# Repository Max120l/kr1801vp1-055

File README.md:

# A replacement for the КР1801ВП1-055

The 055 is a Soviet gate-array bus transceiver: sixteen bidirectional lines plus
three unidirectional buffers, in a 42-pin through-hole package with the pins in
four staggered rows. It cannot be bought, and the only machine known to use it
is the **Elektronika MS 0511 (UKNC)**,
where it is **D22** — sitting between the peripheral processor and the MPI bus,
so when it fails the machine fails in ways that look like everything except a
transceiver.

This repository works out what the chip does, proves a substitute built from
catalogue parts behaves identically, and lists what to buy.

*The part and its replacement, at the same scale. Left: the original, date code
8905, with its pins in the four staggered rows that took three board revisions
to get right. Right: rev C, carrying two 74AHCT245 and a 74AHCT125 in
essentially the original's footprint.*

**Status: built, fitted, and proven — cold and hot.**

A substitute on adapter revision C runs as D22 in the machine this project came
from. It passes the machine's own ТЕСТИРОВАНИЕ fourteen times with ОШИБОК 0, and
a purpose-built bus soak moved **107 MiB through the chip in 1719 passes with
zero errors** — fourteen million of them transitions in which all sixteen lines
reverse at once, which is the one case this design cannot reproduce the
original's answer to. The last 90 passes were run with the board deliberately
heated until it was too hot to touch.

That matters because the fault was thermal and nothing else: the original ran
about ten minutes from cold, died, and recovered within seconds of being cooled.
It was localised two independent ways in September 2026 — cooling D22 alone kept
the machine up, and a CPU-side RAM canary (onerom-1801re2, `diag/canary`) stayed
clean for hundreds of passes while the peripheral processor behind D22 died hot.

Details, figures and what is still unmeasured:
[TESTING.md](docs/TESTING.md#4-the-result).

*Adapter revision C in the socketed D22 site of the MS 0511. The three chips are
the two 74AHCT245 and the 74AHCT125; the board stands about 10 mm above the
motherboard, so check what sits above the site before closing the case.*

## The two findings

**It has no state.** Every cell in the die schematic is a gate, a buffer or an
inverter — no flip-flop, no latch, no clock, no feedback path. That was the
question gating this project, because a stateful control block would have forced
a programmable part. It does not: three ordinary chips reproduce it exactly.

**It does not invert.** Each path carries an even number of inversions — four in
the low byte, two in the high byte, zero in the three-bit buffer. The `nA0–nA15`
pin naming records the bus's active-low convention, not an inversion across this
part. So the substitute is the **74x245**, not the '640.

That second one is a correction, and it is now settled on hardware rather than
only on the die. Earlier notes in the sibling
[onerom-1801re2](https://github.com/Max120l/onerom-1801re2) repository called
the part inverting and recommended the '640, reasoning from the bus rather than
from the die. Building that would have inverted the machine's entire address and
data bus. `make mutants` builds it deliberately and shows the test rejecting it —
and a '245-based board now runs in the machine, which a non-inverting substitute
for an inverting part could not do.

## The substitute

| ref | part | |
|---|---|---|
| U1, U2 | 74AHCT245 | the sixteen bidirectional lines, one per byte |
| U3 | 74AHCT125 | C0–C2 → A0–A2, permanently enabled |
| C1–C4 | 100 nF × 3, 10 µF | decoupling |

`nA` to the '245 A side, `V`/`W` to the B side, pin 20 straight to `DIR`, pin 41
straight to `/OE`. No glue logic at all. Full pin mapping, part-choice reasoning
and the timing comparison are in [DESIGN.md](docs/DESIGN.md).

## Proving it

```console
$ make check                 # substitute vs the original's own gate-array cells
60 checks, 0 mismatches
EQUIVALENT

$ make mutants               # and the test can actually fail
  caught      MUTANT_INVERTING
  caught      MUTANT_DIR
  caught      MUTANT_C_GATED
all mutants caught
```

The reference model is structural: it instantiates the k1801 project's own cell
library, wired the way the die schematic wires it, rather than describing what
the chip is believed to do. Needs Icarus Verilog.

The machine then agreed with the simulation: a board built to this design runs
as D22, and all three mutants above describe mistakes that would have stopped it
running at all — see [TESTING.md](docs/TESTING.md#4-the-result).

## Files

| | |
|---|---|
| [docs/LOGIC.md](docs/LOGIC.md) | what the chip does, traced cell by cell, with the delays |
| [docs/DESIGN.md](docs/DESIGN.md) | the substitute: parts, pin mapping, timing, what is lost |
| [docs/TESTING.md](docs/TESTING.md) | bench check, the proof, and bringing it up in the machine |
| [adapter/](adapter/README.md) | the 42-pin adapter board: generator, routing, gerbers |
| [bustest/](bustest/README.md) | a FODOS volume of adversarial bus patterns, for the worst case ТЕСТИРОВАНИЕ never produces |
| `rtl/vp1_055_orig.v` | the original, from its own cells |
| `rtl/vp1_055_repl.v` | the substitute, from gate primitives |
| `rtl/lib_1801.v` | the k1801 cell library, vendored unmodified |
| `sim/tb_equiv.v` | the equivalence testbench |

## What is not done

- **The PCB is at revision C** — [adapter/](adapter/README.md): a 31 × 32 mm
  two-layer board with the three chips on top and a 42-pin field in the
  measured four-row site geometry underneath, generated and routed by script,
  gerbers included. Revision A was fabricated and did not fit: it mirrored the
  two sides, and the real package's sides are translated copies (rows
  10 · 11 · 10 · 11 with pin 1 top-left, pin 1 in the inner row). Rev C
  corrects the field, and is the revision now fabricated and running in the
  machine.
- **No scope has ever been on the nOE release edge**, of either part. It is the
  one claim in [DESIGN.md](docs/DESIGN.md#timing) still resting on reasoning
  rather than measurement — though a repair that survives a hot worst-case soak
  is strong circumstantial evidence the margin is there. See
  [TESTING.md](docs/TESTING.md#1-the-polarity-check).
- **The delay stagger is still not reproduced**, and now demonstrably does not
  need to be — at least not cold. The original spread its two bytes 7.5 ns apart
  to limit the supply transient when sixteen drivers switch; two identical '245s
  switch together, and the answer here is decoupling. Thirteen million
  deliberate worst-case transitions have now gone through without a bad bit, so
  this is a solved problem rather than an out-voted one. Hot is still untested.

## Credits

The die schematic, the pin description and the cell library are the work of the
[1801BM1/k1801](https://github.com/1801BM1/k1801) project, which reverse
engineered this and a dozen sibling chips from die photographs. None of this
would be possible without it. See [THIRD-PARTY.md](THIRD-PARTY.md).

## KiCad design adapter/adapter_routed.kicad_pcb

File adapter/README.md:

# The adapter board

A 31 × 32 mm two-layer board that plugs into the socketed D22 site and carries
the substitute: two 74AHCT245 for the sixteen bidirectional lines, one
74AHCT125 for C0–C2 → A0–A2, decoupling, and underneath a field of 42 pins in
the original package's pattern. No glue logic — pin 20 goes straight to the
'245s' DIR (its sense already matches: high = nA drives V/W) and pin 41 to
their /OE. The logic is the one proven equivalent in `sim/`.

*Rev C fitted. The site is socketed with individual machined receptacles, as
described under Form factor in [DESIGN.md](../docs/DESIGN.md#form-factor), so
the original, a sourced replacement and this board all plug into the same
holes.*

`vp1-055-adapter-gerbers.zip` is the fab package (two layers, 0.2 mm tracks,
0.15 mm clearance, 0.7/0.3 mm vias, GND pours — any prototype fab).
`adapter_routed.kicad_pcb` is the routed board: 330 segments, 18 vias, every
connection routed, DRC clean.

## Routing practice

Checked against the usual two-layer rules (JLCPCB's routing best-practice
list, September 2026):

| rule | this board |
|---|---|
| signal width 8–10 mil | 0.2 mm (8 mil) everywhere |
| power wider | VCC/GND at 0.3 mm wherever the neighbours allow (about half their length); the rest 0.2 mm. Three AHCT chips draw a few tens of mA, so 8 mil is electrically fine either way |
| clearance ≥ 4 mil | 0.15 mm (6 mil) minimum, measured |
| 45° bends, no acute angles | 274 bends at 45°, 6 right angles, no acute ones |
| via ring ≥ 0.18–0.25 mm | 0.7 mm pad on a 0.3 mm drill: 0.2 mm ring |
| hole-to-hole ≥ 0.2 mm | 0.53 mm minimum |
| copper-to-edge ≥ 0.2 mm | pours stop 0.5 mm inside the edge, everything else more |
| reference plane / return path | solid GND pour on the bottom (≈600 mm², 60 % of the board) under the top-layer signal runs, a smaller one on top, stitched by the GND pins and vias |
| decoupling next to the VCC pin | each 100 nF within 3.6 mm of its chip's VCC pin; 10 µF bulk at the '125 |
| 3W spacing | not met in the bus bundles (0.35 mm centre-to-centre). Irrelevant at these edge rates and lengths; noted for honesty |
| silk ≥ 1 mm text, clear of pads | 1 mm text, pads knocked out of the silk in the export |
| DRC zero errors | yes, with the design's own rules loaded (see `polish_adapter.py` for why that matters) |

## The site, as measured

The КР1801ВП1 package is through-hole, 42 pins in **four staggered rows**:

| | |
|---|---|
| pitch within a row | 2.5 mm |
| consecutive pin numbers along a side | 1.25 mm (they alternate rows) |
| inner row to outer row, same side | 2.5 mm |
| outer row to outer row | 25.0 mm |
| pins | 0.5 mm square; standard machined receptacles fit |
| numbering | pin 1 at the dimple corner, **inner** row; down the left side, up the right (DIP order) |
| rows | with pin 1 top-left, **10 · 11 · 10 · 11** from left to right. The two sides are *translated* copies, not mirror images: the 11-pin row (the one that reaches the end positions) is the **inner** row on the pin-1 side and the **outer** row on the pin-22 side. Pins 1 and 21 are inboard, pins 22 and 42 outboard. |

**Revision C** is the current board (`REV C` on both silks). Revision A was
fabricated with the two sides mirrored (11 · 10 · 10 · 11): its right side
fits the site, its left side has the two rows swapped. Revision B guessed the
parity the other way round (11 · 10 · 11 · 10) and was never fabricated. Rev A
boards remain usable as the bench carrier in
[TESTING.md](../docs/TESTING.md) if the left-side pins are wired instead of
plugged.

Measured on the MS 0511 board in September 2026. If a different board or
package revision disagrees, the numbers live in one dictionary at the top of
`build_adapter.py`.

## Parts

Also as [`BOM.csv`](BOM.csv), with quantities, DigiKey and Mouser numbers
and the 42 socket receptacles for the machine side.

| ref | part | package |
|---|---|---|
| U1, U2 | 74AHCT245 (SN74AHCT245PWR) | TSSOP-20 |
| U3 | 74AHCT125 (SN74AHCT125PWR) | TSSOP-14 |
| C1–C3 | 100 nF | 0603 |
| C4 | 10 µF | 0805 |
| J1 | 42 PCB pins, Ø0.51 mm with a 1.17 mm flange (Mill-Max 3128-1-00-21-00-00-08-0) | single pins, soldered from the top |
| socket | 42 receptacles for Ø0.46–0.51 mm pins in a 1.0–1.1 mm hole (Harwin H3153-01) | one per hole on the MS 0511 |

The pin and the receptacle are a matched pair: the H3153-01 is specified for
0.46–0.51 mm pins and the 3128 pin is 0.51 mm. Ordinary machined-pin header
strips are *not* a safe substitute unless measured — Mill-Max's 2.54 mm
headers have 0.61 mm tails and their 1.27 mm headers 0.43 mm, both outside
the receptacle's range. The receptacle needs a 1.0–1.1 mm hole on the
machine; check the site with a 1.0 mm drill shank before ordering.

TSSOP because that is what fits inside the site outline; SOIC would need the
board to overhang the chip ends by ~10 mm, and the D22 neighbourhood is
crowded. 0.65 mm pitch hand-solders fine with flux and a drag.

Use **AHCT**, not HC/HCT or AC: TTL-level inputs (the bus and the ВМ2 are
TTL-compatible), and the speed is in the same band as the original — see
`docs/DESIGN.md` for the timing comparison.

## Building the files

```
./run.sh          # KiCad 7 python, kicad-cli, Java, freerouting.jar, xvfb-run
```

`build_adapter.py` writes the board from the geometry and the netlist;
Freerouting routes it (`search.sh` tries a few placement nudges until every
connection completes); `finish_adapter.py` imports the routes (parsing the
session file itself — pcbnew's importer only works inside the GUI), runs DRC
and saves; `polish_adapter.py` widens the power traces where clearance
allows, adds the GND pours and runs DRC again; `kicad-cli` exports gerbers
and drill. The zip is what goes to the fab; the routed `.kicad_pcb` is there
for anyone who wants to look or move things.

One trap: netclass rules live in the project file, which this pipeline does
not have, so a freshly loaded board falls back to KiCad's 0.25/0.2 mm
defaults and DRC then flags every track. The scripts restore the design's
rules before checking; do the same if you open the board elsewhere.

## Assembly

1. Fit the socket on the machine first: one machined receptacle per hole, 42
   of them (singles, not strips — strips are 2.54 mm and drift off the 2.5 mm
   holes within a row).
2. Solder the SMD parts on the top of the adapter.
3. Push the 42 pins through the adapter from the top, **long (6.35 mm) end
   down**: the flange stops on the top pad and is soldered there, the short
   2.5 mm stub stays above the board. Use the socketed site as the jig (pins
   plugged into the receptacles first, adapter lowered onto them, then
   soldered) so they stay straight; then trim the pins to ~3.5 mm below the
   board, which is what the receptacle takes.
4. Plug in with the pin-1 corner (square pad, marked on the silk) at the
   dimple corner of the site.

## Acceptance test

Boot FODOS and run the canary (`diag/canary` in onerom-1801re2) on a warm
machine for twenty minutes: the bell keeps ticking and the log is clean. That
is the exact failure the original chip had, so it is the exact test.

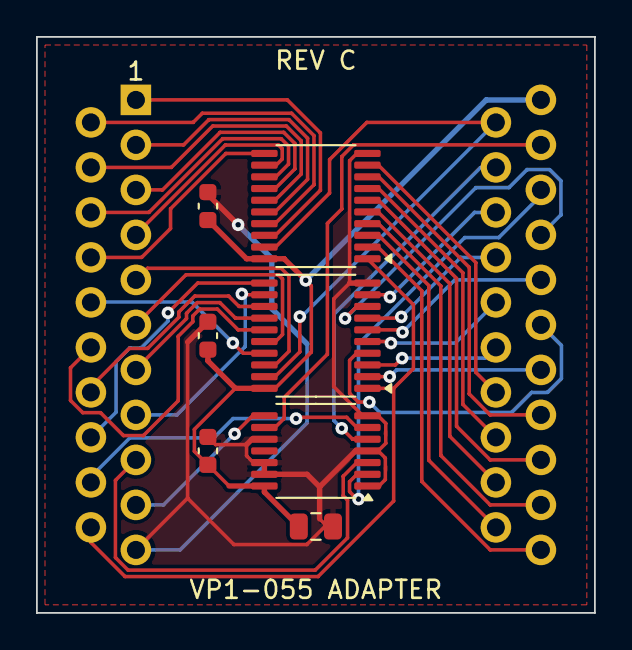
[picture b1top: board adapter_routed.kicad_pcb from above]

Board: 2 copper layers, 31.0 x 32.0 mm, 8 parts (0 on the bottom side), 42 nets.

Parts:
C1, C2, C3: 100n; C_0603_1608Metric
C4: 10u; C_0805_2012Metric
J1: VP1-055 site; VP1-055_site
U1, U2: 74AHCT245; TSSOP-20_4.4x6.5mm_P0.65mm
U3: 74AHCT125; TSSOP-14_4.4x5mm_P0.65mm

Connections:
A0: J1.17, U3.3
A1: J1.18, U3.6
A2: J1.19, U3.8
C0: J1.38, U3.2
C1: J1.39, U3.5
C2: J1.40, U3.9
DIR: J1.20, U1.1, U2.1
GND: C1.2, C2.2, C3.2, C4.2, J1.21, U1.10, U2.10, U3.1, U3.4, U3.7, U3.10, U3.12, U3.13
V0: J1.1, U1.18
V1: J1.2, U1.17
V2: J1.3, U1.16
V3: J1.4, U1.15
V4: J1.5, U1.14
V5: J1.6, U1.13
V6: J1.7, U1.12
V7: J1.8, U1.11
VCC: C1.1, C2.1, C3.1, C4.1, J1.42, U1.20, U2.20, U3.14
W0: J1.9, U2.18
W1: J1.10, U2.17
W2: J1.11, U2.16
W3: J1.12, U2.15
W4: J1.13, U2.14
W5: J1.14, U2.13
W6: J1.15, U2.12
W7: J1.16, U2.11
nA0: J1.22, U1.2
nA1: J1.23, U1.3
nA2: J1.24, U1.4
nA3: J1.25, U1.5
nA4: J1.26, U1.6
nA5: J1.27, U1.7
nA6: J1.28, U1.8
nA7: J1.29, U1.9
nA8: J1.30, U2.2
nA9: J1.31, U2.3
nA10: J1.32, U2.4
nA11: J1.33, U2.5
nA12: J1.34, U2.6
nA13: J1.35, U2.7
nA14: J1.36, U2.8
nA15: J1.37, U2.9
nOE: J1.41, U1.19, U2.19

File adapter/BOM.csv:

ref,qty,value,package,manufacturer part,DigiKey,Mouser,notes
"U1, U2",2,74AHCT245,TSSOP-20,TI SN74AHCT245PWR,296-1118-1-ND,595-SN74AHCT245PWR,"non-inverting; AHCT only (not '640, not HC/HCT)"
U3,1,74AHCT125,TSSOP-14,TI SN74AHCT125PWR,296-1108-1-ND,595-SN74AHCT125PWR,"or Nexperia 74AHCT125PW (same pinout); or 3 sections of a non-inverting '244/'541 with enables grounded"
"C1, C2, C3",3,100 nF 50 V X7R,0603,Samsung CL10B104KB8NNNC,1276-1000-1-ND,187-CL10B104KB8NNNC,decoupling; any 0603 100 nF X7R is fine
C4,1,10 uF 16 V X5R,0805,Samsung CL21A106KOQNNNG,1276-6455-1-ND,187-CL21A106KOQNNNG,bulk; any 0805 10 uF is fine
J1,42,PCB pin 0.51 mm dia,single pin with 1.17 mm flange,Mill-Max 3128-1-00-21-00-00-08-0,3128-100210000080-ND,575-3128-1-00-21-00-00-08-0,"flange on top of the adapter, 6.35 mm end down through the 1.0 mm hole, trim to ~3.5 mm below the board; 3128-3-00-21-00-00-08-0 (DigiKey ED11474-ND) is the same pin 7 mm longer, stocked deeper. If the site was socketed with generic machined receptacle strips, the cheapest pins are the male round-pin header of the same family, plastic removed - test-fit one first"
socket (on the MS 0511),42,receptacle for 0.46-0.51 mm pins,single; 1.0-1.1 mm hole,Harwin H3153-01,952-1457-ND,855-H3153-01,"one per hole; needs the board holes to be at least 1.0 mm - check with a 1.0 mm drill shank first. Alternative: generic machined (round-hole) receptacles broken into singles, which is what the first build used; then use their matching round-pin header as J1"
